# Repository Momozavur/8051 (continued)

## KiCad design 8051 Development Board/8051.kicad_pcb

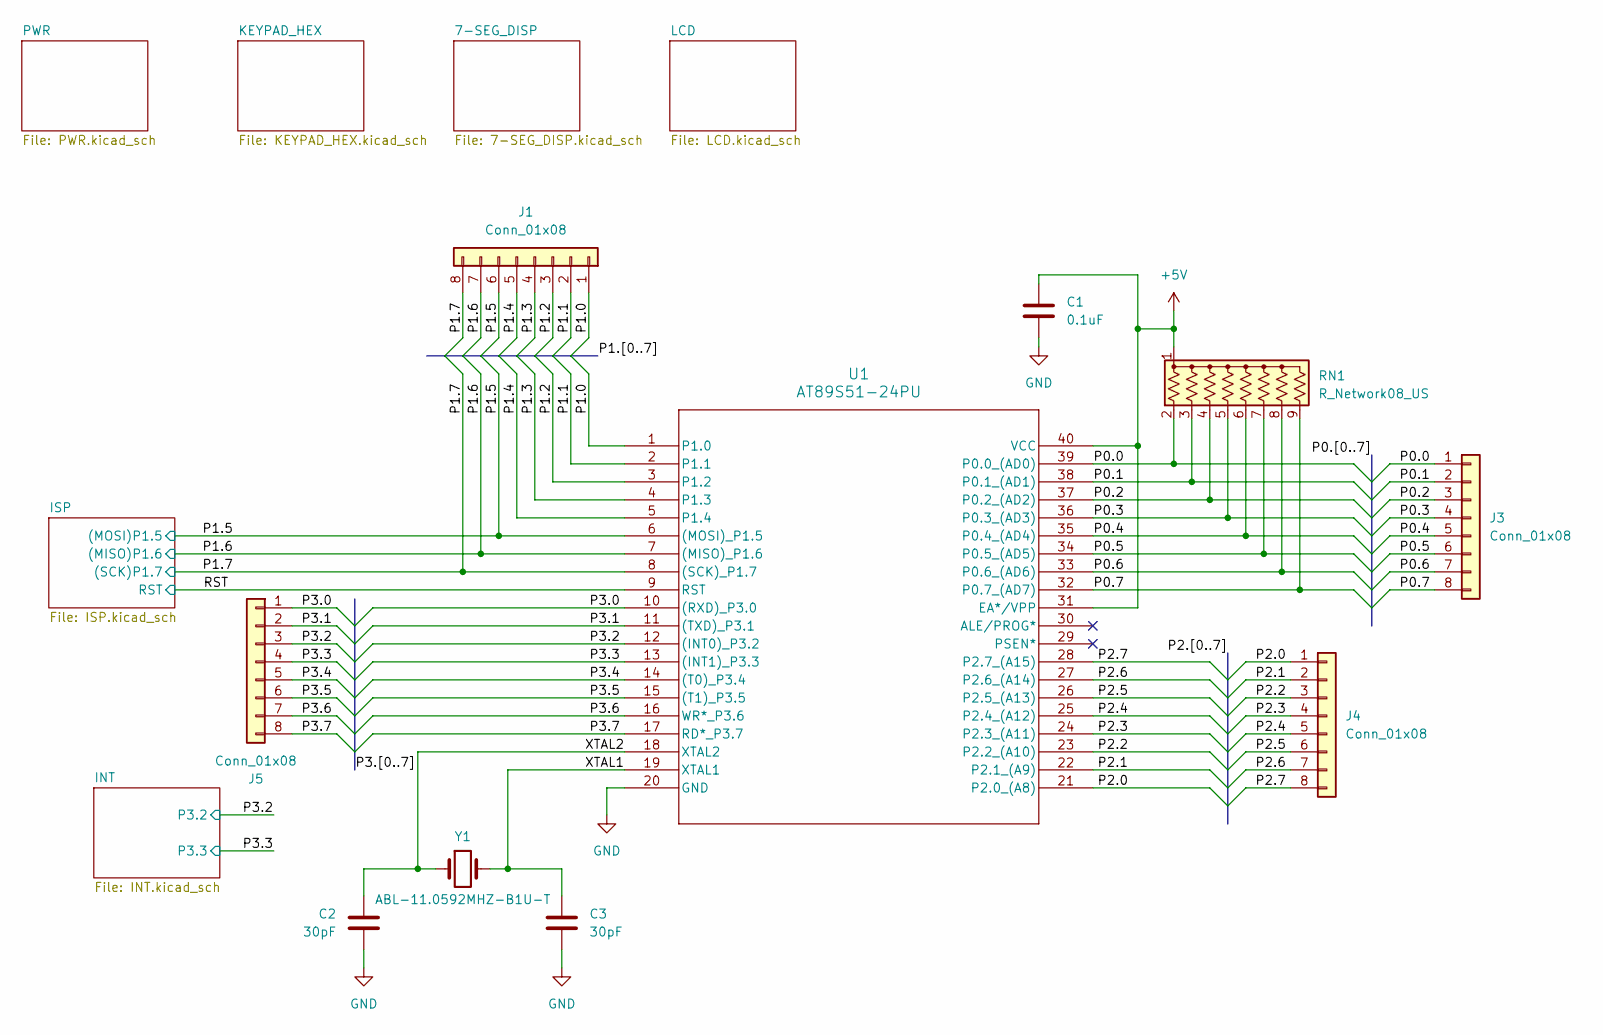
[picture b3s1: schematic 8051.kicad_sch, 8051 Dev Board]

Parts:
C1: 0.1uF; C_1206_3216Metric_Pad1.33x1.80mm_HandSolder
C2, C3: 30pF; C_1206_3216Metric_Pad1.33x1.80mm_HandSolder
J1, J3, J4, J5: Conn_01x08; PinHeader_1x08_P2.54mm_Vertical
RN1: R_Network08_US; R_Array_SIP9
U1: AT89S51-24PU; 40P6_ATM
Y1: ABL-11.0592MHZ-B1U-T; Crystal_HC49-4H_Vertical

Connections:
+5V: C1.1, RN1.1 (common), U1.31 (EA*/VPP), U1.40 (VCC); also elsewhere on the board
/P0.0: J3.1, RN1.2 (R1), U1.39 (P0.0_(AD0))
/P0.1: J3.2, RN1.3 (R2), U1.38 (P0.1_(AD1))
/P0.2: J3.3, RN1.4 (R3), U1.37 (P0.2_(AD2))
/P0.3: J3.4, RN1.5 (R4), U1.36 (P0.3_(AD3))
/P0.4: J3.5, RN1.6 (R5), U1.35 (P0.4_(AD4))
/P0.5: J3.6, RN1.7 (R6), U1.34 (P0.5_(AD5))
/P0.6: J3.7, RN1.8 (R7), U1.33 (P0.6_(AD6))
/P0.7: J3.8, RN1.9 (R8), U1.32 (P0.7_(AD7))
/P1.0: J1.1, U1.1 (P1.0)
/P1.1: J1.2, U1.2 (P1.1)
/P1.2: J1.3, U1.3 (P1.2)
/P1.3: J1.4, U1.4 (P1.3)
/P1.4: J1.5, U1.5 (P1.4)
/P1.5: J1.6, U1.6 ((MOSI)_P1.5); also elsewhere on the board
/P1.6: J1.7, U1.7 ((MISO)_P1.6); also elsewhere on the board
/P1.7: J1.8, U1.8 ((SCK)_P1.7); also elsewhere on the board
/P2.0: J4.1, U1.21 (P2.0_(A8))
/P2.1: J4.2, U1.22 (P2.1_(A9))
/P2.2: J4.3, U1.23 (P2.2_(A10))
/P2.3: J4.4, U1.24 (P2.3_(A11))
/P2.4: J4.5, U1.25 (P2.4_(A12))
/P2.5: J4.6, U1.26 (P2.5_(A13))
/P2.6: J4.7, U1.27 (P2.6_(A14))
/P2.7: J4.8, U1.28 (P2.7_(A15))
/P3.0: J5.1, U1.10 ((RXD)_P3.0)
/P3.1: J5.2, U1.11 ((TXD)_P3.1)
/P3.2: J5.3, U1.12 ((INT0)_P3.2); also elsewhere on the board
/P3.3: J5.4, U1.13 ((INT1)_P3.3); also elsewhere on the board
/P3.4: J5.5, U1.14 ((T0)_P3.4)
/P3.5: J5.6, U1.15 ((T1)_P3.5)
/P3.6: J5.7, U1.16 (WR*_P3.6)
/P3.7: J5.8, U1.17 (RD*_P3.7)
/RST: U1.9 (RST); also elsewhere on the board
/XTAL1: C3.1, U1.19 (XTAL1), Y1.2
/XTAL2: C2.1, U1.18 (XTAL2), Y1.1
GND: C1.2, C2.2, C3.2, U1.20 (GND); also elsewhere on the board

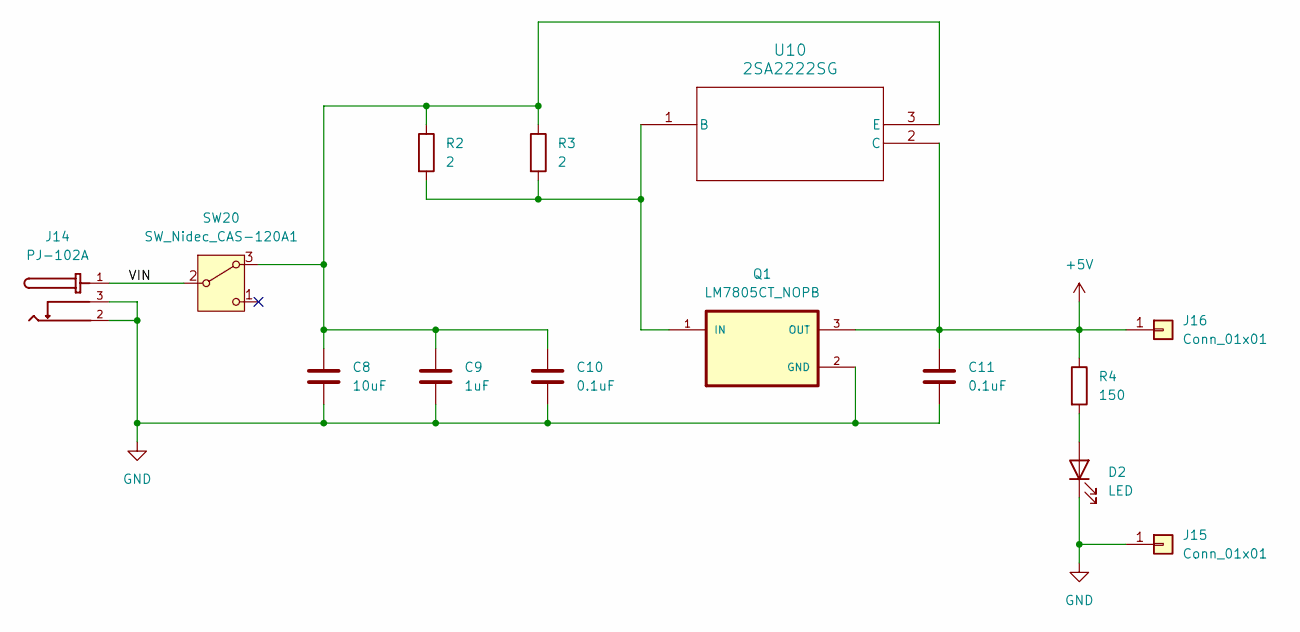
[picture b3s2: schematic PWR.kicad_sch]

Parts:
C8: 10uF; C_1206_3216Metric_Pad1.33x1.80mm_HandSolder
C9: 1uF; C_1206_3216Metric_Pad1.33x1.80mm_HandSolder
C10, C11: 0.1uF; C_1206_3216Metric_Pad1.33x1.80mm_HandSolder
D2: LED; LED_D3.0mm
J14: PJ-102A; BarrelJack_CUI_PJ-102AH_Horizontal
J15, J16: Conn_01x01; PinHeader_1x01_P2.54mm_Vertical
Q1: LM7805CT_NOPB; TO254P1054X470X2600-3; PARTREV LTR
R2, R3: 2; R_1206_3216Metric_Pad1.30x1.75mm_HandSolder
R4: 150; R_1206_3216Metric_Pad1.30x1.75mm_HandSolder
SW20: SW_Nidec_CAS-120A1; 500SSP1S1M2QEA
U10: 2SA2222SG; TO-220F-3SG_15P87X10P16_ONS

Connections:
+5V: C11.1, J16.1, Q1.3 (OUT), R4.1, U10.2 (C); also elsewhere on the board
/PWR/VIN: J14.1, SW20.2 (B)
GND: C8.2, C9.2, C10.2, C11.2, D2.1 (K), J14.2, J14.3, J15.1, Q1.2 (GND); also elsewhere on the board
unnamed: D2.2 (A), R4.2
unnamed: Q1.1 (IN), R2.2, R3.2, U10.1 (B)
unnamed: C8.1, C9.1, C10.1, R2.1, R3.1, SW20.3 (A), U10.3 (E)

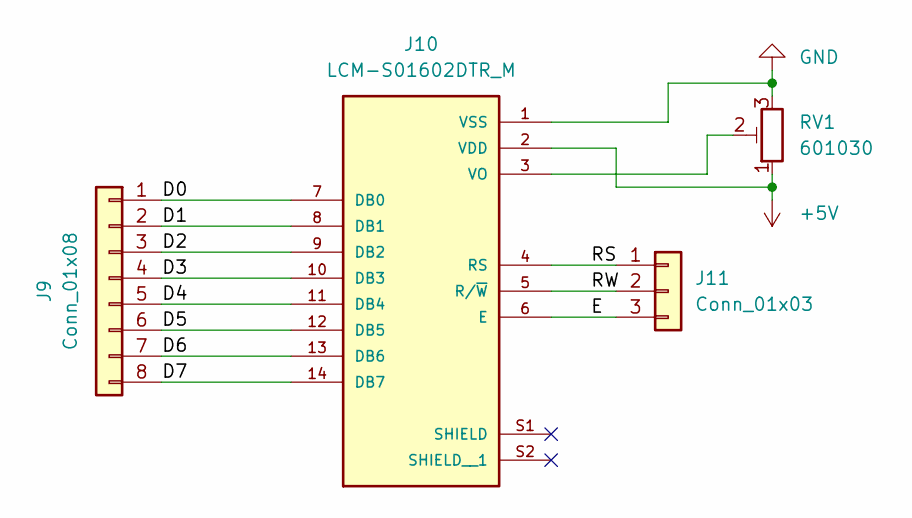
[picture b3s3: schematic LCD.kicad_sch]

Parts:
J9: Conn_01x08; PinHeader_1x08_P2.54mm_Vertical
J10: LCM-S01602DTR_M; LCD_LCM-S01602DTR_M; PARTREV 9/11/02
J11: Conn_01x03; PinHeader_1x03_P2.54mm_Vertical
RV1: 601030; 601030_AVX

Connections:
+5V: J10.2 (VDD), RV1.1; also elsewhere on the board
/LCD/D0: J9.1, J10.7 (DB0)
/LCD/D1: J9.2, J10.8 (DB1)
/LCD/D2: J9.3, J10.9 (DB2)
/LCD/D3: J9.4, J10.10 (DB3)
/LCD/D4: J9.5, J10.11 (DB4)
/LCD/D5: J9.6, J10.12 (DB5)
/LCD/D6: J9.7, J10.13 (DB6)
/LCD/D7: J9.8, J10.14 (DB7)
/LCD/E: J10.6 (E), J11.3
/LCD/RS: J10.4 (RS), J11.1
/LCD/RW: J10.5 (R/~W), J11.2
GND: J10.1 (VSS), RV1.3; also elsewhere on the board
unnamed: J10.3 (VO), RV1.2

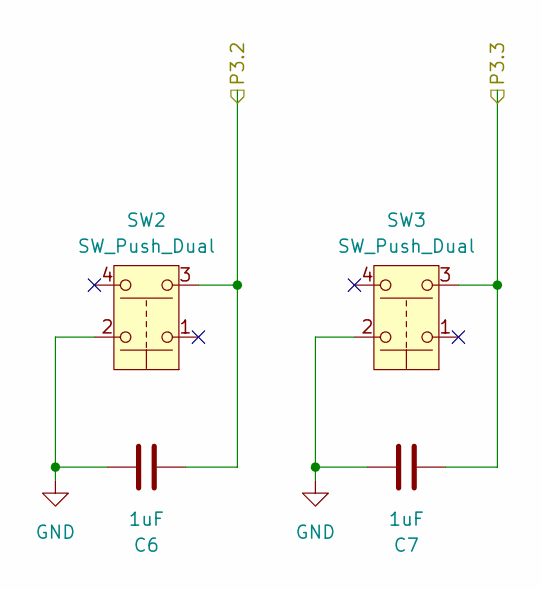
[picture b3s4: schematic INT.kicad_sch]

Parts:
C6, C7: 1uF; C_1206_3216Metric_Pad1.33x1.80mm_HandSolder
SW2, SW3: SW_Push_Dual; SW_PUSH_6mm_H7.3mm

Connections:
/P3.2: C6.1, SW2.3; also elsewhere on the board
/P3.3: C7.2, SW3.3; also elsewhere on the board
GND: C6.2, C7.1, SW2.2, SW3.2; also elsewhere on the board

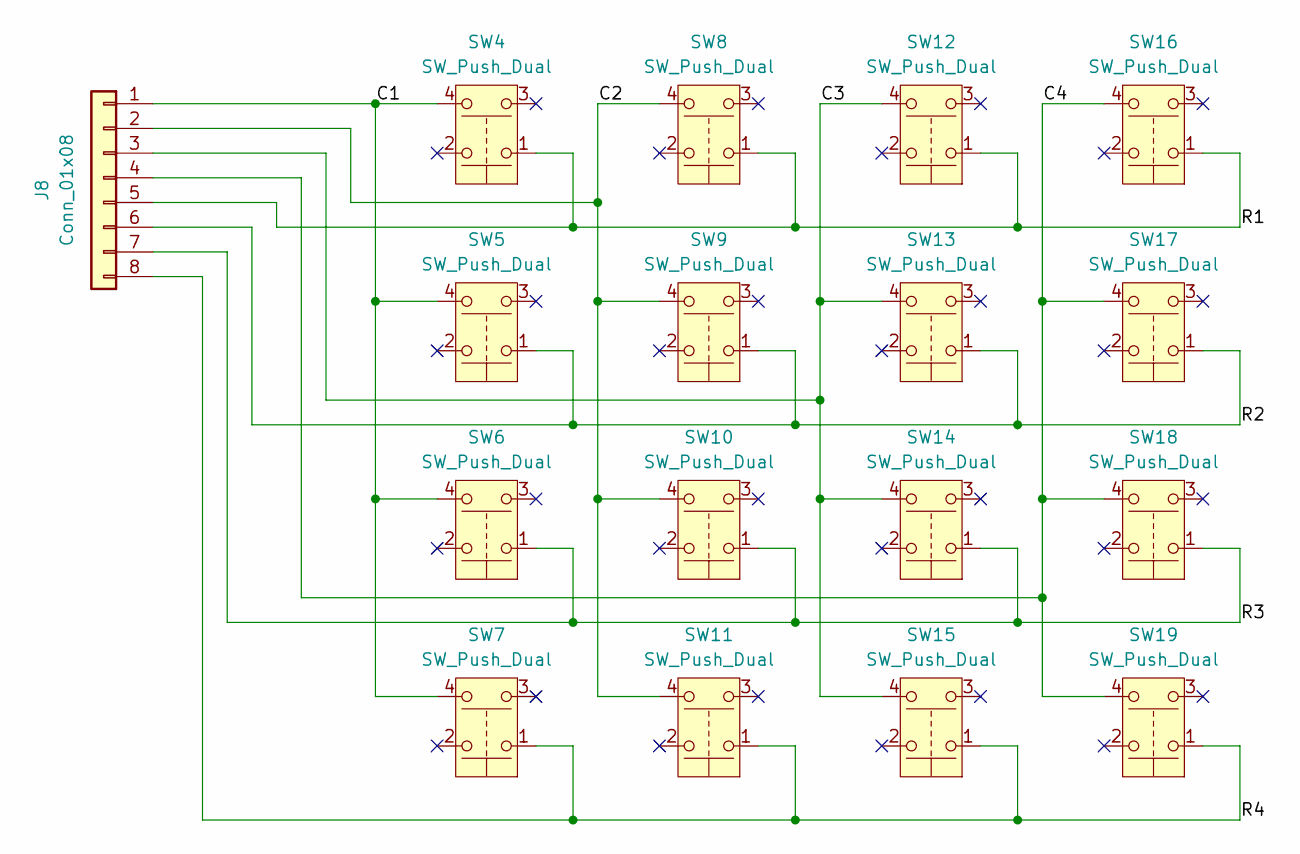
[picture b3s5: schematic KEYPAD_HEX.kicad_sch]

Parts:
J8: Conn_01x08; PinHeader_1x08_P2.54mm_Vertical
SW4, SW5, SW6, SW7, SW8, SW9, SW10, SW11, SW12, SW13, SW14, SW15, SW16, SW17, SW18, SW19: SW_Push_Dual; SW_PUSH_6mm_H7.3mm

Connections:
/KEYPAD_HEX/C1: J8.1, SW4.4, SW5.4, SW6.4, SW7.4
/KEYPAD_HEX/C2: J8.2, SW8.4, SW9.4, SW10.4, SW11.4
/KEYPAD_HEX/C3: J8.3, SW12.4, SW13.4, SW14.4, SW15.4
/KEYPAD_HEX/C4: J8.4, SW16.4, SW17.4, SW18.4, SW19.4
/KEYPAD_HEX/R1: J8.5, SW4.1, SW8.1, SW12.1, SW16.1
/KEYPAD_HEX/R2: J8.6, SW5.1, SW9.1, SW13.1, SW17.1
/KEYPAD_HEX/R3: J8.7, SW6.1, SW10.1, SW14.1, SW18.1
/KEYPAD_HEX/R4: J8.8, SW7.1, SW11.1, SW15.1, SW19.1

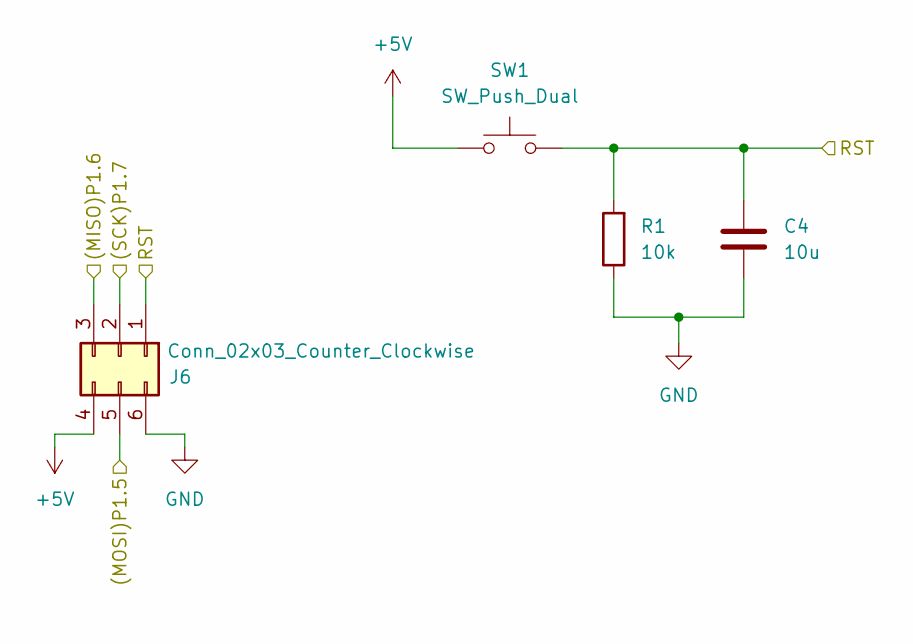
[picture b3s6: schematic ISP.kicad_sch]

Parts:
C4: 10u; C_1206_3216Metric_Pad1.33x1.80mm_HandSolder
J6: Conn_02x03_Counter_Clockwise; PinHeader_2x03_P2.54mm_Vertical
R1: 10k; R_1206_3216Metric_Pad1.30x1.75mm_HandSolder
SW1: SW_Push_Dual; SW_PUSH_6mm_H7.3mm

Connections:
+5V: J6.4, SW1.1; also elsewhere on the board
/P1.5: J6.5; also elsewhere on the board
/P1.6: J6.3; also elsewhere on the board
/P1.7: J6.2; also elsewhere on the board
/RST: C4.1, J6.1, R1.2, SW1.2; also elsewhere on the board
GND: C4.2, J6.6, R1.1; also elsewhere on the board

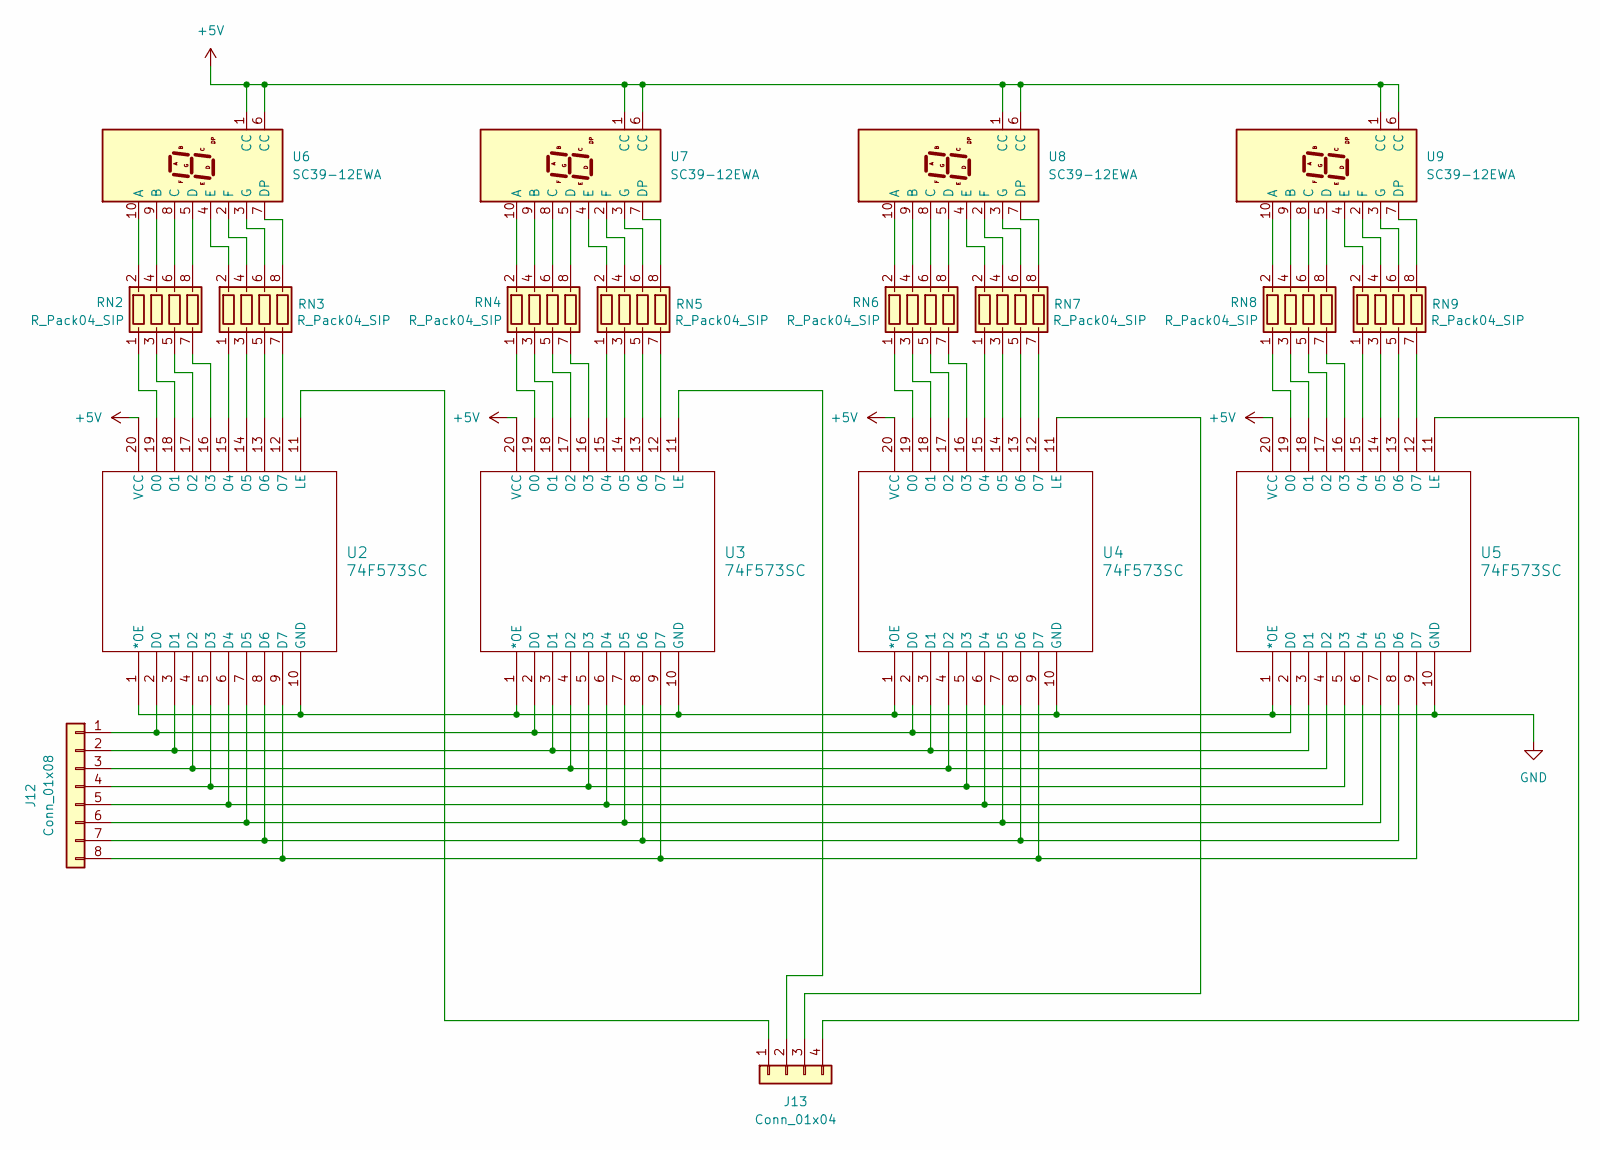
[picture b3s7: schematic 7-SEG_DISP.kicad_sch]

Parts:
J12: Conn_01x08; PinHeader_1x08_P2.54mm_Vertical
J13: Conn_01x04; PinHeader_1x04_P2.54mm_Vertical
RN2, RN3, RN4, RN5, RN6, RN7, RN8, RN9: R_Pack04_SIP; R_Array_SIP8
U2, U3, U4, U5: 74F573SC; SOIC20_12P7X5P4_ONS
U6, U7, U8, U9: SC39-12EWA; 7SegmentLED_LTS6760_LTS6780

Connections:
+5V: U2.20 (VCC), U3.20 (VCC), U4.20 (VCC), U5.20 (VCC), U6.1 (CC), U6.6 (CC), U7.1 (CC), U7.6 (CC), U8.1 (CC), U8.6 (CC), U9.1 (CC), U9.6 (CC); also elsewhere on the board
GND: U2.1 (*OE), U2.10 (GND), U3.1 (*OE), U3.10 (GND), U4.1 (*OE), U4.10 (GND), U5.1 (*OE), U5.10 (GND); also elsewhere on the board
unnamed: J12.1, U2.2 (D0), U3.2 (D0), U4.2 (D0), U5.2 (D0)
unnamed: J12.2, U2.3 (D1), U3.3 (D1), U4.3 (D1), U5.3 (D1)
unnamed: J12.3, U2.4 (D2), U3.4 (D2), U4.4 (D2), U5.4 (D2)
unnamed: J12.4, U2.5 (D3), U3.5 (D3), U4.5 (D3), U5.5 (D3)
unnamed: J12.5, U2.6 (D4), U3.6 (D4), U4.6 (D4), U5.6 (D4)
unnamed: J12.6, U2.7 (D5), U3.7 (D5), U4.7 (D5), U5.7 (D5)
unnamed: J12.7, U2.8 (D6), U3.8 (D6), U4.8 (D6), U5.8 (D6)
unnamed: J12.8, U2.9 (D7), U3.9 (D7), U4.9 (D7), U5.9 (D7)
unnamed: J13.1, U2.11 (LE)
unnamed: J13.2, U3.11 (LE)
unnamed: J13.3, U4.11 (LE)
unnamed: J13.4, U5.11 (LE)
unnamed: RN2.1 (R1.1), U2.19 (O0)
unnamed: RN2.2 (R1.2), U6.10 (A)
unnamed: RN2.3 (R2.1), U2.18 (O1)
unnamed: RN2.4 (R2.2), U6.9 (B)
unnamed: RN2.5 (R3.1), U2.17 (O2)
unnamed: RN2.6 (R3.2), U6.8 (C)
unnamed: RN2.7 (R4.1), U2.16 (O3)
unnamed: RN2.8 (R4.2), U6.5 (D)
unnamed: RN3.1 (R1.1), U2.15 (O4)
unnamed: RN3.2 (R1.2), U6.4 (E)
unnamed: RN3.3 (R2.1), U2.14 (O5)
unnamed: RN3.4 (R2.2), U6.2 (F)
unnamed: RN3.5 (R3.1), U2.13 (O6)
unnamed: RN3.6 (R3.2), U6.3 (G)
unnamed: RN3.7 (R4.1), U2.12 (O7)
unnamed: RN3.8 (R4.2), U6.7 (DP)
unnamed: RN4.1 (R1.1), U3.19 (O0)
unnamed: RN4.2 (R1.2), U7.10 (A)
unnamed: RN4.3 (R2.1), U3.18 (O1)
unnamed: RN4.4 (R2.2), U7.9 (B)
unnamed: RN4.5 (R3.1), U3.17 (O2)
unnamed: RN4.6 (R3.2), U7.8 (C)
unnamed: RN4.7 (R4.1), U3.16 (O3)
unnamed: RN4.8 (R4.2), U7.5 (D)
unnamed: RN5.1 (R1.1), U3.15 (O4)
unnamed: RN5.2 (R1.2), U7.4 (E)
unnamed: RN5.3 (R2.1), U3.14 (O5)
unnamed: RN5.4 (R2.2), U7.2 (F)
unnamed: RN5.5 (R3.1), U3.13 (O6)
unnamed: RN5.6 (R3.2), U7.3 (G)
unnamed: RN5.7 (R4.1), U3.12 (O7)
unnamed: RN5.8 (R4.2), U7.7 (DP)
unnamed: RN6.1 (R1.1), U4.19 (O0)
unnamed: RN6.2 (R1.2), U8.10 (A)
unnamed: RN6.3 (R2.1), U4.18 (O1)
unnamed: RN6.4 (R2.2), U8.9 (B)
unnamed: RN6.5 (R3.1), U4.17 (O2)
unnamed: RN6.6 (R3.2), U8.8 (C)
unnamed: RN6.7 (R4.1), U4.16 (O3)
unnamed: RN6.8 (R4.2), U8.5 (D)
unnamed: RN7.1 (R1.1), U4.15 (O4)
unnamed: RN7.2 (R1.2), U8.4 (E)
unnamed: RN7.3 (R2.1), U4.14 (O5)
unnamed: RN7.4 (R2.2), U8.2 (F)
unnamed: RN7.5 (R3.1), U4.13 (O6)
unnamed: RN7.6 (R3.2), U8.3 (G)
unnamed: RN7.7 (R4.1), U4.12 (O7)
unnamed: RN7.8 (R4.2), U8.7 (DP)
unnamed: RN8.1 (R1.1), U5.19 (O0)
unnamed: RN8.2 (R1.2), U9.10 (A)
unnamed: RN8.3 (R2.1), U5.18 (O1)
unnamed: RN8.4 (R2.2), U9.9 (B)
unnamed: RN8.5 (R3.1), U5.17 (O2)
unnamed: RN8.6 (R3.2), U9.8 (C)
unnamed: RN8.7 (R4.1), U5.16 (O3)
unnamed: RN8.8 (R4.2), U9.5 (D)
unnamed: RN9.1 (R1.1), U5.15 (O4)
unnamed: RN9.2 (R1.2), U9.4 (E)
unnamed: RN9.3 (R2.1), U5.14 (O5)
unnamed: RN9.4 (R2.2), U9.2 (F)
unnamed: RN9.5 (R3.1), U5.13 (O6)
unnamed: RN9.6 (R3.2), U9.3 (G)
unnamed: RN9.7 (R4.1), U5.12 (O7)
unnamed: RN9.8 (R4.2), U9.7 (DP)

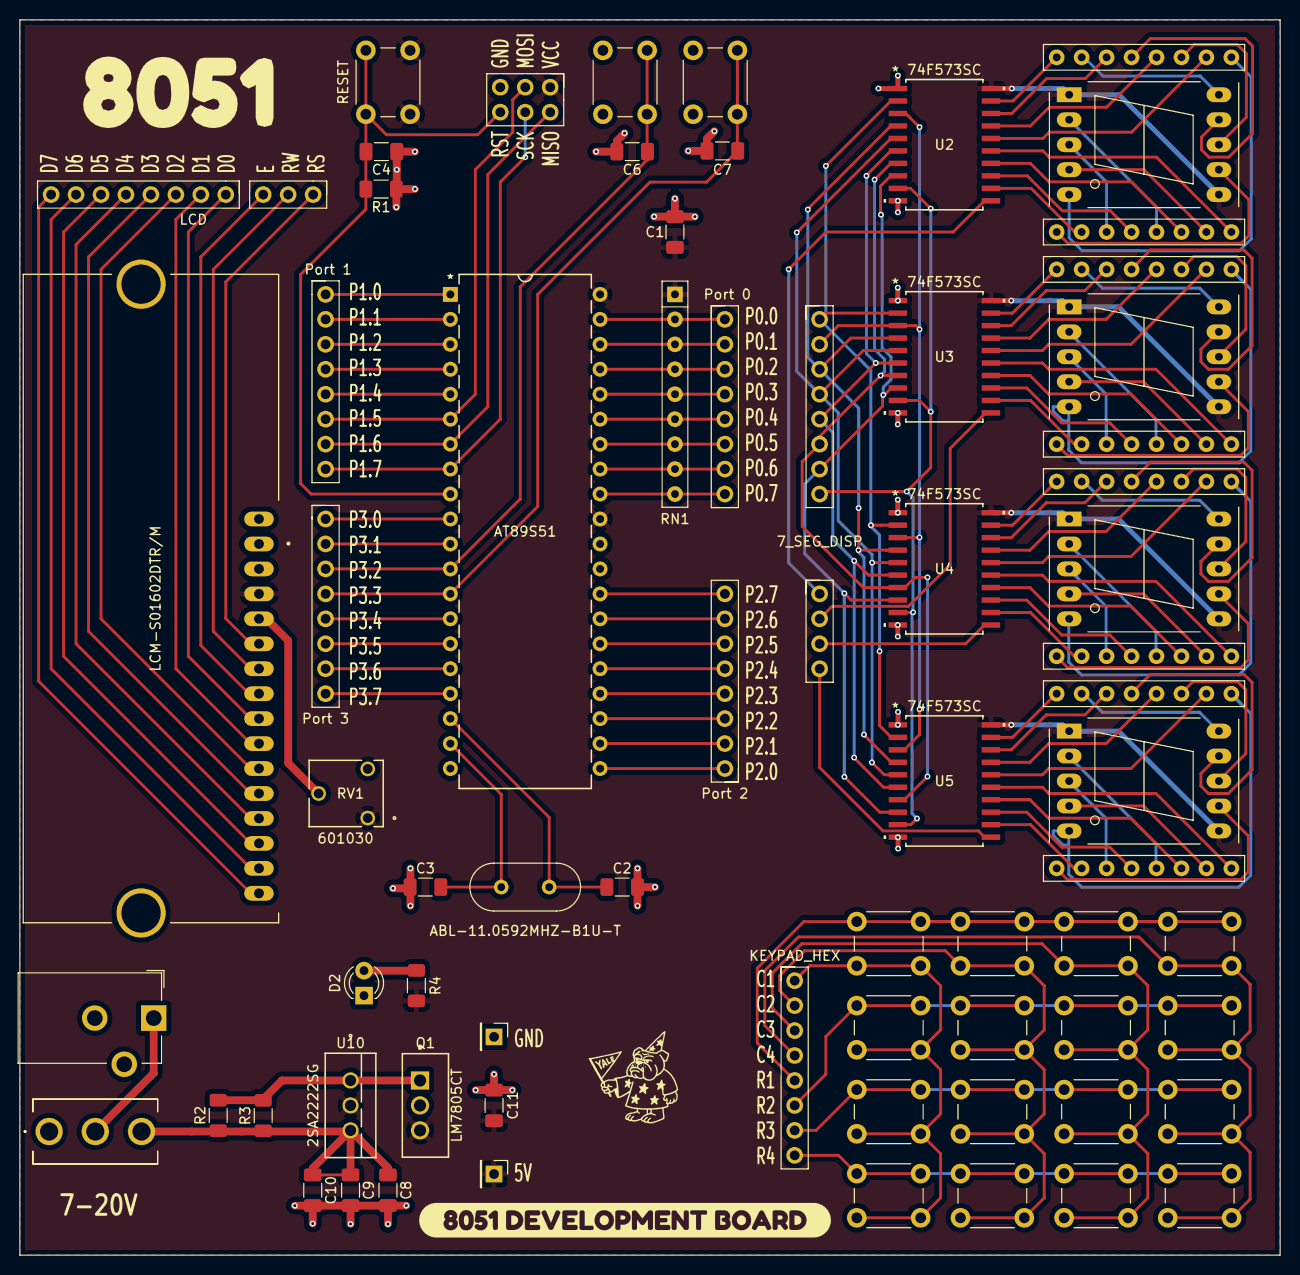
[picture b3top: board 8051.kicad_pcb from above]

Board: 2 copper layers, 128.3 x 125.7 mm, 73 parts (0 on the bottom side), 137 nets.

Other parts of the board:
kibuzzard-68D8BB38: G***; kibuzzard-68D8BB38
kibuzzard-68D8BC51: G***; kibuzzard-68D8BC51

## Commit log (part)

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2025-09-22 test
2025-09-25 power
2025-09-25 breakout board
2025-09-25 traces
2025-09-26 silkscreen bs
2025-09-26 done
2025-09-26 gerbers
2025-09-26 layout
2025-09-26 5v power plane
2025-09-28 dev board gerbers
2025-10-06 gerber fix
2025-12-17 resistors
2025-12-30 fixed footprint 8051
2026-01-06 ultra
2026-01-12 nets
